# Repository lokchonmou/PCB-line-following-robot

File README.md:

# PCB-line-following-robot
the aim of this project is to make an Arduino robot or DFrobot miniQ 4WD robot like PCB robot, but using cheap material and adding I2C to the car for extension

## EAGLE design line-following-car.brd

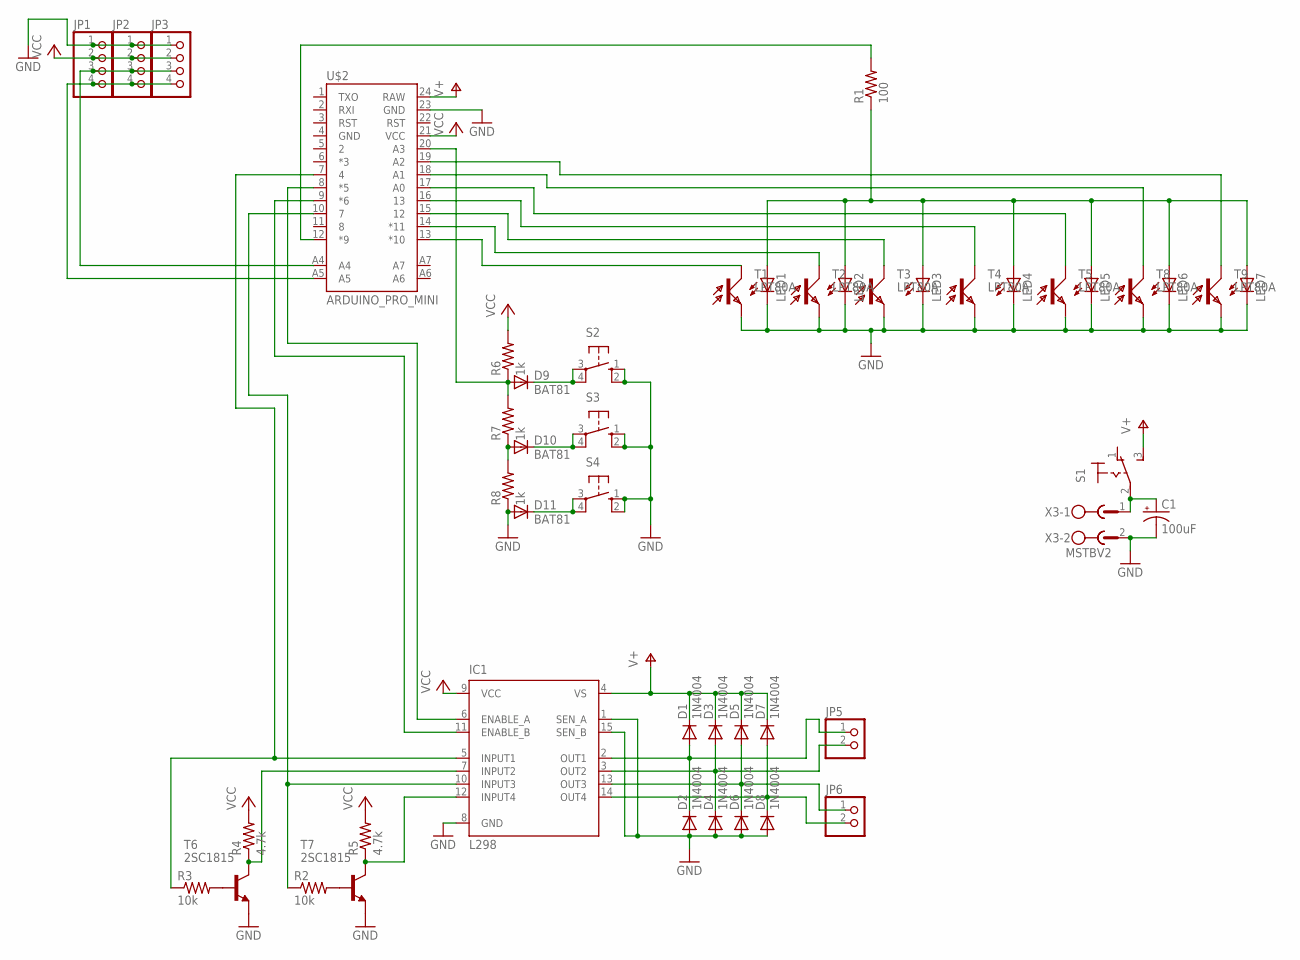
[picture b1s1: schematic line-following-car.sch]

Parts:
C1: 100uF; E2-4
D1, D2, D3, D4, D5, D6, D7, D8: 1N4004; DO41-10
D9, D10, D11: BAT81; DO34-7
IC1: L298; MULTIWATT-15
JP1, JP2, JP3: PINHD-1X4; 1X04
JP5, JP6: PINHD-1X2; 1X02
LED1, LED2, LED3, LED4, LED5, LED6, LED7: LED3MM
R1: 100; 0204/5
R2, R3: 10k; 0204/5
R4, R5: 4.7k; 0204/5
R6, R7, R8: 1k; 0207/7
S1: 320-916
S2, S3, S4: 10-XX; B3F-10XX
T1, T2, T3, T4, T5, T8, T9: LPT80A
T6, T7: 2SC1815; TO92-ECB
U$2: ARDUINO_PRO_MINI
X3: MSTBV2

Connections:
GND: C1.-, D2.A, D4.A, D6.A, D8.A, D11.A, IC1.1 (SEN_A), IC1.8 (GND), IC1.15 (SEN_B), JP1.1, JP2.1, JP3.1, LED1.K (C), LED2.K (C), LED3.K (C), LED4.K (C), LED5.K (C), LED6.K (C), LED7.K (C), R8.1, S2.1 (S), S2.2 (S1), S3.1 (S), S3.2 (S1), S4.1 (S), S4.2 (S1), T1.E, T2.E, T3.E, T4.E, T5.E, T6.E, T7.E, T8.E, T9.E, U$2.23 (GND), X3.2
unnamed: LED1.A, LED2.A, LED3.A, LED4.A, LED5.A, LED6.A, LED7.A, R1.1
unnamed: R2.2, T7.B
unnamed: R1.2, U$2.12 (*9)
unnamed: R3.2, T6.B
unnamed: T1.C, U$2.13 (*10)
unnamed: T2.C, U$2.14 (*11)
unnamed: T3.C, U$2.15 (12)
unnamed: T4.C, U$2.16 (13)
unnamed: T5.C, U$2.17 (A0)
unnamed: D1.A, D2.C, IC1.2 (OUT1), JP5.1
unnamed: IC1.7 (INPUT2), R4.1, T6.C
unnamed: IC1.12 (INPUT4), R5.1, T7.C
unnamed: D3.A, D4.C, IC1.3 (OUT2), JP5.2
unnamed: IC1.5 (INPUT1), R3.1, U$2.7 (4)
unnamed: IC1.6 (ENABLE_A), U$2.8 (*5)
unnamed: IC1.10 (INPUT3), R2.1, U$2.10 (7)
unnamed: D9.A, R6.1, R7.2, U$2.20 (A3)
unnamed: D5.A, D6.C, IC1.13 (OUT3), JP6.1
unnamed: D7.A, D8.C, IC1.14 (OUT4), JP6.2
unnamed: D10.A, R7.1, R8.2
unnamed: D9.C, S2.3, S2.4 (P1)
unnamed: JP1.4, JP2.4, JP3.4, U$2.A5
unnamed: IC1.11 (ENABLE_B), U$2.9 (*6)
unnamed: D10.C, S3.3, S3.4 (P1)
unnamed: C1.+, S1.2, X3.1
unnamed: D11.C, S4.3, S4.4 (P1)
unnamed: JP1.3, JP2.3, JP3.3, U$2.A4
unnamed: T8.C, U$2.18 (A1)
unnamed: T9.C, U$2.19 (A2)
V+: D1.C, D3.C, D5.C, D7.C, IC1.4 (VS), S1.3 (S), U$2.24 (RAW)
VCC: IC1.9 (VCC), JP1.2, JP2.2, JP3.2, R4.2, R5.2, R6.2, U$2.21 (VCC)

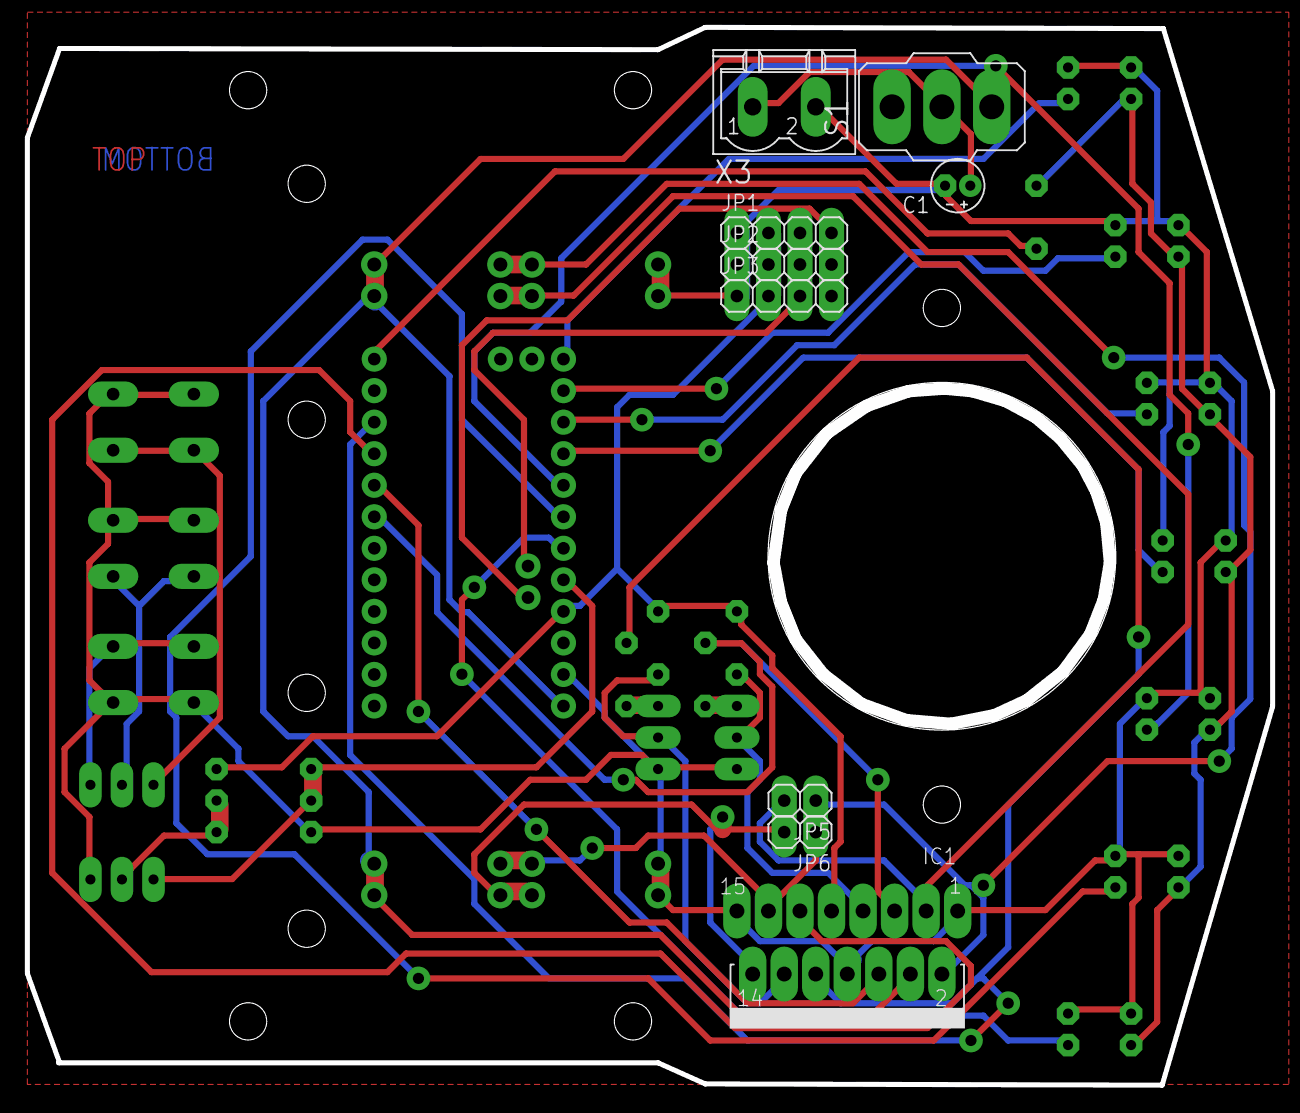
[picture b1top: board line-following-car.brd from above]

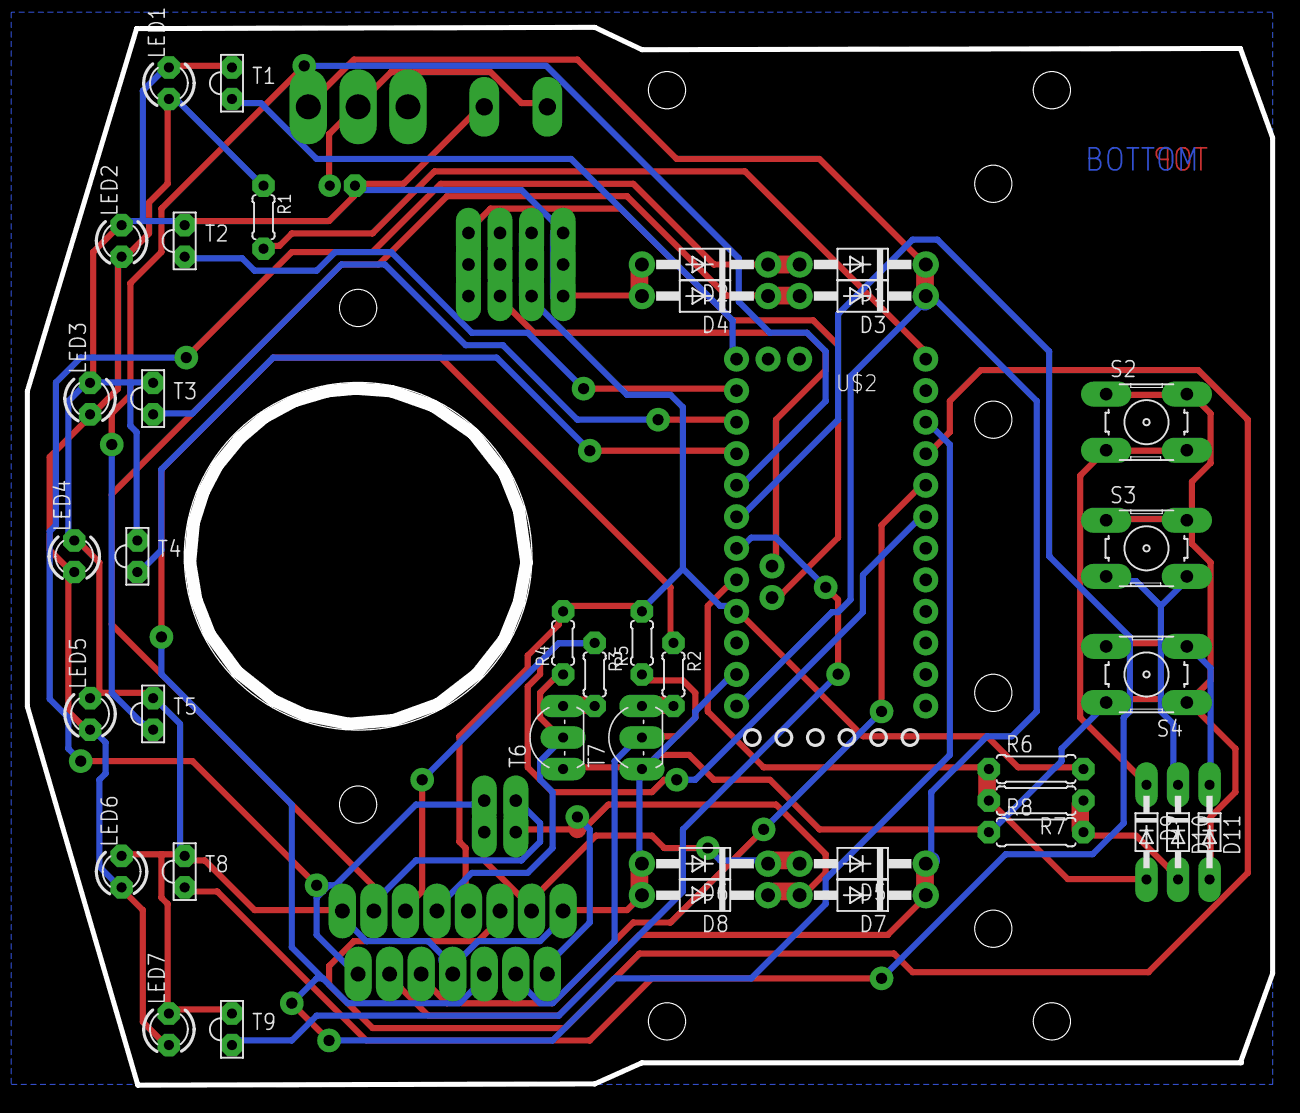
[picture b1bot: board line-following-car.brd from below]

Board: 2 copper layers, 99.7 x 84.6 mm, 48 parts (39 on the bottom side), 32 nets.

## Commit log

2015-12-18 version 1
    using Eagle light to make, double layer, DIY PCB, but the space is too
    limiting….go to make a version 2 with 2 PCB

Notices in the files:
parts and their libraries:
SparkFun-Boards_0: Licensing: Creative Commons ShareAlike 4.0 International - https://creativecommons.org/licenses/by-sa/4.0
